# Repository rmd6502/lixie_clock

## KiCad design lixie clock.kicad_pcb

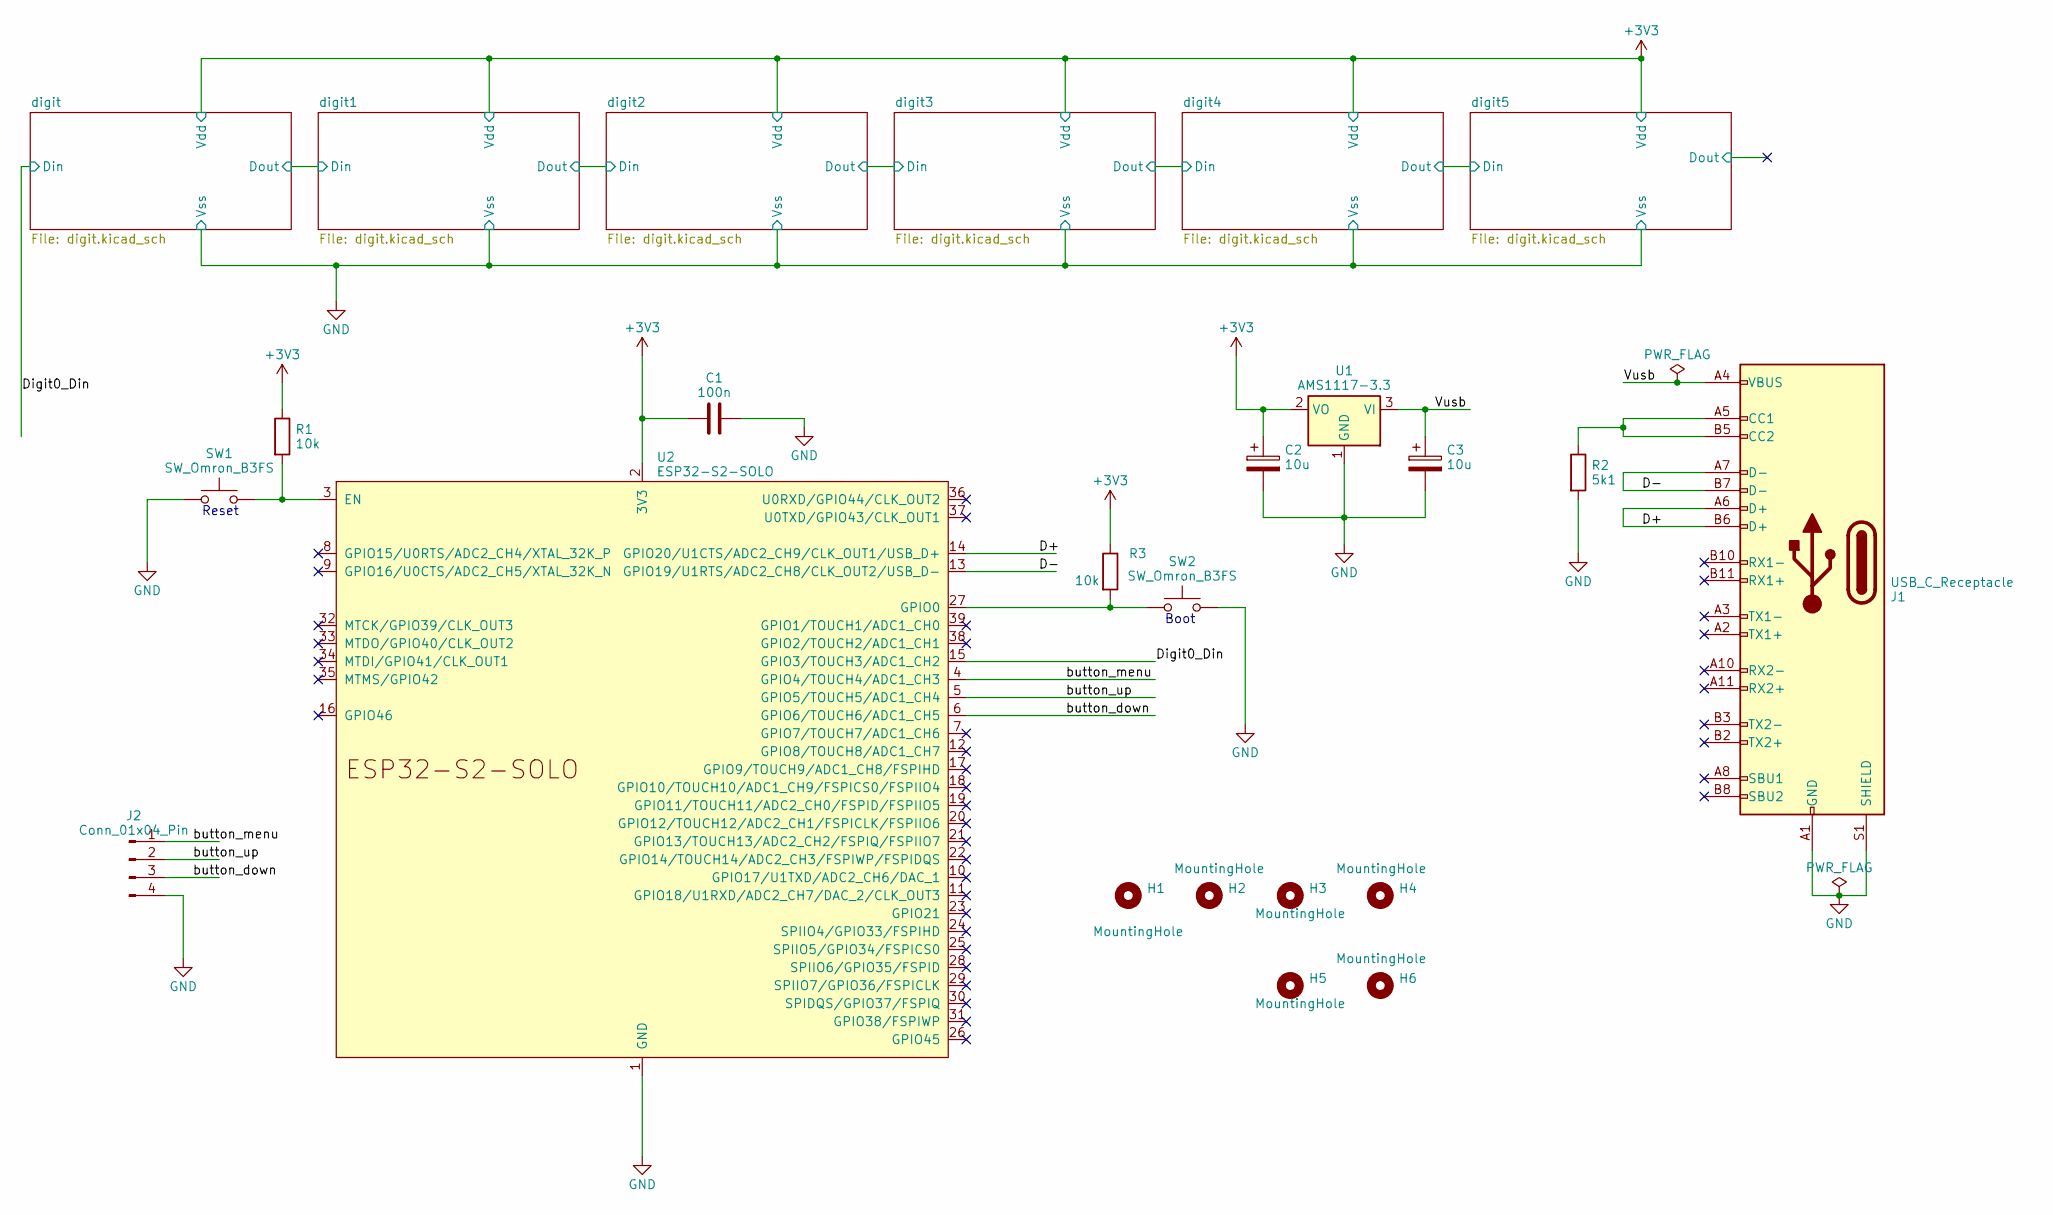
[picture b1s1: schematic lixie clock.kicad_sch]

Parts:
C1: 100n; C_0603_1608Metric; LCSC C282519
C2, C3: 10u; CP_Elec_4x5.4; LCSC C4747969
H1, H2, H3, H4, H5, H6: MountingHole; MountingHole_3.2mm_M3
J1: USB_C_Receptacle; USB_C_Receptacle_HRO_TYPE-C-31-M-12; LCSC C709357
J2: Conn_01x04_Pin; Molex_KK-254_AE-6410-04A_1x04_P2.54mm_Vertical; LCSC C541858
R1, R3: 10k; R_0402_1005Metric; LCSC C2074114
R2: 5k1; R_0402_1005Metric; LCSC C274895
SW1, SW2: SW_Omron_B3FS; SW_SPST_Omron_B3FS-100xP; LCSC C271753
U1: AMS1117-3.3; SOT-223-3_TabPin2; LCSC C5181460
U2: ESP32-S2-SOLO; LCSC C3040594

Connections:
+3V3: C1.1, C2.1, R1.1, R3.1, U1.2 (VO), U2.2 (3V3); also elsewhere on the board
/D+: J1.A6 (D+), J1.B6 (D+), U2.14 (GPIO20/U1CTS/ADC2_CH9/CLK_OUT1/USB_D+)
/D-: J1.A7 (D-), J1.B7 (D-), U2.13 (GPIO19/U1RTS/ADC2_CH8/CLK_OUT2/USB_D-)
/Digit0_Din: U2.15 (GPIO3/TOUCH3/ADC1_CH2); also elsewhere on the board
/Vusb: C3.1, J1.A4 (VBUS), J1.A9 (VBUS), J1.B4 (VBUS), J1.B9 (VBUS), U1.3 (VI)
/button_down: J2.3, U2.6 (GPIO6/TOUCH6/ADC1_CH5)
/button_menu: J2.1, U2.4 (GPIO4/TOUCH4/ADC1_CH3)
/button_up: J2.2, U2.5 (GPIO5/TOUCH5/ADC1_CH4)
GND: C1.2, C2.2, C3.2, J1.A1 (GND), J1.A12 (GND), J1.B1 (GND), J1.B12 (GND), J1.S1 (SHIELD), J2.4, R2.2, SW1.1, SW2.2, U1.1 (GND), U2.1 (GND), U2.40 (GND), U2.41 (GND); also elsewhere on the board
unnamed: J1.A5 (CC1), J1.B5 (CC2), R2.1
unnamed: R1.2, SW1.2, U2.3 (EN)
unnamed: R3.2, SW2.1, U2.27 (GPIO0)

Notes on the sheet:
Reset
Boot

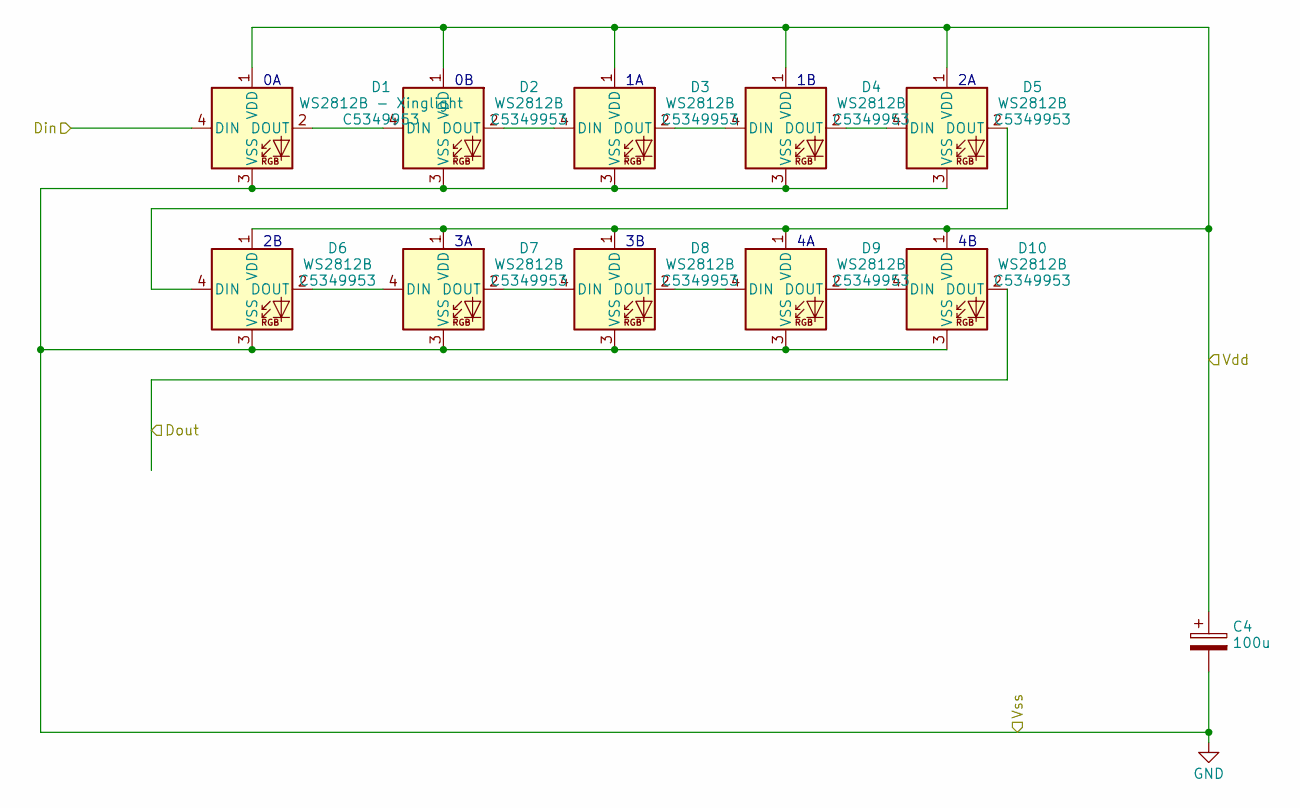
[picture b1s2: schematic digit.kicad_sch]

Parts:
C4: 100u; CP_Elec_4x5.4; LCSC C4747963
D1: WS2812B - Xinglight; LED_WD2812B-1010_PLCC4_1.0x1.0; LCSC C5349953
D2, D3, D4, D5, D6, D7, D8, D9, D10: WS2812B; LED_WD2812B-1010_PLCC4_1.0x1.0; LCSC C5349953

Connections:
+3V3: C4.1, D1.1 (VDD), D2.1 (VDD), D3.1 (VDD), D4.1 (VDD), D5.1 (VDD), D6.1 (VDD), D7.1 (VDD), D8.1 (VDD), D9.1 (VDD), D10.1 (VDD); also elsewhere on the board
/Digit0_Din: D1.4 (DIN); also elsewhere on the board
/digit/Dout: D10.2 (DOUT); also elsewhere on the board
GND: C4.2, D1.3 (VSS), D2.3 (VSS), D3.3 (VSS), D4.3 (VSS), D5.3 (VSS), D6.3 (VSS), D7.3 (VSS), D8.3 (VSS), D9.3 (VSS), D10.3 (VSS); also elsewhere on the board
unnamed: D1.2 (DOUT), D2.4 (DIN)
unnamed: D2.2 (DOUT), D3.4 (DIN)
unnamed: D3.2 (DOUT), D4.4 (DIN)
unnamed: D4.2 (DOUT), D5.4 (DIN)
unnamed: D5.2 (DOUT), D6.4 (DIN)
unnamed: D6.2 (DOUT), D7.4 (DIN)
unnamed: D7.2 (DOUT), D8.4 (DIN)
unnamed: D8.2 (DOUT), D9.4 (DIN)
unnamed: D9.2 (DOUT), D10.4 (DIN)

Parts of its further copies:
C5, C6, C7, C8, C9: 100u; CP_Elec_4x5.4; LCSC C4747963
D11, D21, D31, D41, D51: WS2812B - Xinglight; LED_WD2812B-1010_PLCC4_1.0x1.0; LCSC C5349953
D12, D13, D14, D15, D16, D17, D18, D19, D20, D22, D23, D24, D25, D26, D27, D28, D29, D30, D32, D33, D34, D35, D36, D37, D38, D39, D40, D42, D43, D44, D45, D46, D47, D48, D49, D50, D52, D53, D54, D55, D56, D57, D58, D59, D60: WS2812B; LED_WD2812B-1010_PLCC4_1.0x1.0; LCSC C5349953

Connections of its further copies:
+3V3: C5.1, C6.1, C7.1, C8.1, C9.1, D11.1 (VDD), D12.1 (VDD), D13.1 (VDD), D14.1 (VDD), D15.1 (VDD), D16.1 (VDD), D17.1 (VDD), D18.1 (VDD), D19.1 (VDD), D20.1 (VDD), D21.1 (VDD), D22.1 (VDD), D23.1 (VDD), D24.1 (VDD), D25.1 (VDD), D26.1 (VDD), D27.1 (VDD), D28.1 (VDD), D29.1 (VDD), D30.1 (VDD), D31.1 (VDD), D32.1 (VDD), D33.1 (VDD), D34.1 (VDD), D35.1 (VDD), D36.1 (VDD), D37.1 (VDD), D38.1 (VDD), D39.1 (VDD), D40.1 (VDD), D41.1 (VDD), D42.1 (VDD), D43.1 (VDD), D44.1 (VDD), D45.1 (VDD), D46.1 (VDD), D47.1 (VDD), D48.1 (VDD), D49.1 (VDD), D50.1 (VDD), D51.1 (VDD), D52.1 (VDD), D53.1 (VDD), D54.1 (VDD), D55.1 (VDD), D56.1 (VDD), D57.1 (VDD), D58.1 (VDD), D59.1 (VDD), D60.1 (VDD); also elsewhere on the board
/digit1/Dout: D20.2 (DOUT), D21.4 (DIN)
/digit2/Dout: D30.2 (DOUT), D31.4 (DIN)
/digit3/Dout: D40.2 (DOUT), D41.4 (DIN)
/digit4/Dout: D50.2 (DOUT), D51.4 (DIN)
/digit5/Dout: D60.2 (DOUT)
/digit/Dout: D11.4 (DIN); also elsewhere on the board
GND: C5.2, C6.2, C7.2, C8.2, C9.2, D11.3 (VSS), D12.3 (VSS), D13.3 (VSS), D14.3 (VSS), D15.3 (VSS), D16.3 (VSS), D17.3 (VSS), D18.3 (VSS), D19.3 (VSS), D20.3 (VSS), D21.3 (VSS), D22.3 (VSS), D23.3 (VSS), D24.3 (VSS), D25.3 (VSS), D26.3 (VSS), D27.3 (VSS), D28.3 (VSS), D29.3 (VSS), D30.3 (VSS), D31.3 (VSS), D32.3 (VSS), D33.3 (VSS), D34.3 (VSS), D35.3 (VSS), D36.3 (VSS), D37.3 (VSS), D38.3 (VSS), D39.3 (VSS), D40.3 (VSS), D41.3 (VSS), D42.3 (VSS), D43.3 (VSS), D44.3 (VSS), D45.3 (VSS), D46.3 (VSS), D47.3 (VSS), D48.3 (VSS), D49.3 (VSS), D50.3 (VSS), D51.3 (VSS), D52.3 (VSS), D53.3 (VSS), D54.3 (VSS), D55.3 (VSS), D56.3 (VSS), D57.3 (VSS), D58.3 (VSS), D59.3 (VSS), D60.3 (VSS); also elsewhere on the board
unnamed: D11.2 (DOUT), D12.4 (DIN)
unnamed: D12.2 (DOUT), D13.4 (DIN)
unnamed: D13.2 (DOUT), D14.4 (DIN)
unnamed: D14.2 (DOUT), D15.4 (DIN)
unnamed: D15.2 (DOUT), D16.4 (DIN)
unnamed: D16.2 (DOUT), D17.4 (DIN)
unnamed: D17.2 (DOUT), D18.4 (DIN)
unnamed: D18.2 (DOUT), D19.4 (DIN)
unnamed: D19.2 (DOUT), D20.4 (DIN)
unnamed: D21.2 (DOUT), D22.4 (DIN)
unnamed: D22.2 (DOUT), D23.4 (DIN)
unnamed: D23.2 (DOUT), D24.4 (DIN)
unnamed: D24.2 (DOUT), D25.4 (DIN)
unnamed: D25.2 (DOUT), D26.4 (DIN)
unnamed: D26.2 (DOUT), D27.4 (DIN)
unnamed: D27.2 (DOUT), D28.4 (DIN)
unnamed: D28.2 (DOUT), D29.4 (DIN)
unnamed: D29.2 (DOUT), D30.4 (DIN)
unnamed: D31.2 (DOUT), D32.4 (DIN)
unnamed: D32.2 (DOUT), D33.4 (DIN)
unnamed: D33.2 (DOUT), D34.4 (DIN)
unnamed: D34.2 (DOUT), D35.4 (DIN)
unnamed: D35.2 (DOUT), D36.4 (DIN)
unnamed: D36.2 (DOUT), D37.4 (DIN)
unnamed: D37.2 (DOUT), D38.4 (DIN)
unnamed: D38.2 (DOUT), D39.4 (DIN)
unnamed: D39.2 (DOUT), D40.4 (DIN)
unnamed: D41.2 (DOUT), D42.4 (DIN)
unnamed: D42.2 (DOUT), D43.4 (DIN)
unnamed: D43.2 (DOUT), D44.4 (DIN)
unnamed: D44.2 (DOUT), D45.4 (DIN)
unnamed: D45.2 (DOUT), D46.4 (DIN)
unnamed: D46.2 (DOUT), D47.4 (DIN)
unnamed: D47.2 (DOUT), D48.4 (DIN)
unnamed: D48.2 (DOUT), D49.4 (DIN)
unnamed: D49.2 (DOUT), D50.4 (DIN)
unnamed: D51.2 (DOUT), D52.4 (DIN)
unnamed: D52.2 (DOUT), D53.4 (DIN)
unnamed: D53.2 (DOUT), D54.4 (DIN)
unnamed: D54.2 (DOUT), D55.4 (DIN)
unnamed: D55.2 (DOUT), D56.4 (DIN)
unnamed: D56.2 (DOUT), D57.4 (DIN)
unnamed: D57.2 (DOUT), D58.4 (DIN)
unnamed: D58.2 (DOUT), D59.4 (DIN)
unnamed: D59.2 (DOUT), D60.4 (DIN)

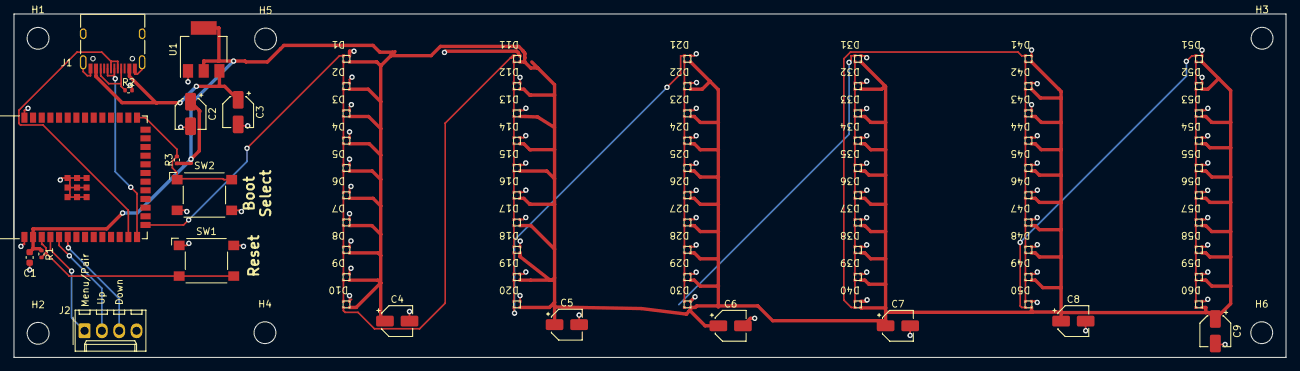
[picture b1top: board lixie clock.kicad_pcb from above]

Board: 2 copper layers, 186.5 x 50.4 mm, 84 parts (0 on the bottom side), 71 nets.
